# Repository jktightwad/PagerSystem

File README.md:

# Pool table pager

Queue pager system for the office pool table, similar to restaurant pagers.
ESP32 pagers talk to a touchscreen base over ESP-NOW (no Wi-Fi network needed),
charge on a stackable pogo-pin dock, and alert with light, buzzer and vibration.

**All sketches are written but not yet compiled or tested on hardware.**
Arduino-ESP32 core 3.x is required.

## Building with PlatformIO
Each test folder is its own PlatformIO project (`platformio.ini` inside it),
using the pioarduino platform for Arduino-ESP32 core 3.x. Open the folder in
VS Code / PlatformIO and pick the environment for your board:
- `lolin32_lite`: WEMOS LOLIN32 Lite (pagers)
- `esp32c3_supermini`: ESP32-C3 SuperMini (temporary base); not available
  for `pager_alert_test`, whose pins only exist on the classic ESP32

From a terminal: `pio run -e esp32c3_supermini -t upload`, then
`pio device monitor`. The folders also still open in the Arduino IDE.

| Folder | What it is |
|---|---|
| `docs/design.md` | Decisions, proposals, open questions |
| `docs/test_plan.md` | Test cases for pairing, queue, docking, radio, web, security, OTA, power |
| `docs/pager_wiring.md` | Pager pin map, power and driver wiring; PN5180 wiring |
| `range_test/` | ESP-NOW range test (base + walker) |
| `pager_firmware/` | Pager firmware (POC): Wi-Fi setup hotspot, per-pager web page (status, tests, demo mode, admin), OTA |
| `pager_alert_test/` | WS2812 ring, beeper, vibration, button, dock/battery readings |
| `pn5180_csn_test/` | Read the HID iCLASS CSN with a PN5180 (no keys) |
| `base_firmware/` | Base firmware (POC): Wi-Fi from `secrets.h`, status page; queue/badge/radio next |
| `enclosure/` | 3D-printed parts (OpenSCAD): pager shell, LED ring test rig, connector fit tester |
| `ota_test/` | Over-the-air update proof of concept (base AP + pager) |

## Libraries
- Adafruit NeoPixel (1.12+) for `pager_alert_test`
- PN5180 by playfultechnology (GPL-3.0) for `pn5180_csn_test`.
  Don't install ATrappmann's PN5180 library at the same time (same header name).

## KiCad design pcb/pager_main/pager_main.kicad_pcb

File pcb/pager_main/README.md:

# Combined pager board (16 LEDs + ESP32-S3 SuperMini) — draft

**Status: placed, routed, GND stitched; DRC has no clearance or unconnected errors
(remaining: silkscreen overlaps/clipping and 1 single-spoke thermal). Not ordered, not tested.**

| Top | Bottom (seen from below) |
|---|---|
|  |  |

54 x 48 mm, 2 layers, M2 holes in all 4 corners (layout D from `layout_study.py`).

- **Top:** 16 × TUOZHAN TZ-5050S2RGB-5V-I4-H1 (LCSC C26167850, allowed in JLC Economic PCBA; the XINGLIGHT part was Standard-only), evenly spaced (22.5°) on a 20.5 mm radius,
  ring turned 19.75° so every LED keeps its own 100 nF cap beside it, clear of the cut-out.
  Passive SMD buzzer Huaneng MLT-8530 (C94599, 8.5 x 8.5 x 3.0 mm, 16 Ω, 2.7 kHz, PWM tone on GP12;
  four pads, + and − on the right, the two left pads are mechanical dummies) and
  the small parts inside the ring; all JLC-assembled.
- **Under:** SuperMini flat on castellated pads, antenna end at the right edge (no copper
  there); B+/B− soldered from the top through 1.1 × 1.6 mm plated oval holes; an
  L-shaped cut-out only where the module's underside parts are (measured: 3.0–11.2 mm
  from the USB end, incl. 0.5 mm clearance). GND pour (no tracks) allowed under the module. Touch (XH-3) and dock
  (XH-2) right-angle connectors, plugs in from the left edge. SS12F44 switch (slider
  down; end-leg spacing 11.2 mm is an ESTIMATE, slotted). Battery and motor wire pads.
- **Spare pins** on an arc outside the LED ring: top-left TX RX 3 6 7 3V3 GND,
  bottom-left 11 10 9 8 VBAT 3V3 GND (labels on both sides where they fit).
- Connectors: pin 1 = GND (square), power last.

Pins: dock GP1, battery GP2, touch GP4, LEDs GP5 (via 330 Ω), buzzer GP12, motor GP13.

## Rebuild
```
python3 build_main.py
ROUTE_OPTIONAL=GND ROUTE_FIRST=U1 ROUTE_MARGIN=0.08 \
  ROUTE_WIDTHS='{"VBAT": 0.3, "BAT+": 0.4, "POGO5V": 0.3, "MOT_-": 0.3, "GND": 0.25}' \
  python3 ../carrier_s3/route_pcb.py pager_main.kicad_pcb
python3 ../carrier_s3/stitch_gnd.py pager_main.kicad_pcb 2.0
python3 ../carrier_s3/join_gnd.py pager_main.kicad_pcb
python3 ../carrier_s3/remove_dangling.py pager_main.kicad_pcb
python3 fix_anchors.py pager_main.kicad_pcb && python3 check_netlist.py
python3 easyeda_prep.py pager_main.kicad_pcb     # before importing into EasyEDA (and after any refill)
sh export_fab.sh && sh render.sh pcb_top.png pcb_bottom.png
```
Routing takes a while (randomised retries; `ROUTE_SEED` picks the sequence). GND gets tracks
where they fit (routed last, best effort), plus pours on both layers, ~200 stitching vias and
`join_gnd.py` for any piece left over; `remove_dangling.py` drops stitch vias left in pour
islands. The current board is seed 3 with the transistor / divider block ripped up and
re-routed (`../carrier_s3/reroute_area.py`, box 14,19-30,31, GND fan-out vias for R2, R7, Q2,
C1), because those four GND pads were walled in by tracks.

## Assembly
Single-sided JLC Economic PCBA (top side): LEDs, caps, resistors, MOSFETs, diode, buzzer. Hand-soldered:
SuperMini, switch and the two through-hole JST-XH connectors (under the board).
A two-sided variant with SMD connectors (DEALON XH-3PWB / XH-2PWB) can still be built with
`PAGER_SMD_CONN=1 python3 build_main.py` and exported with `sh export_fab.sh smdconn` (Standard PCBA);
its files were removed to avoid uploading the wrong set.

## Current board (v4)
Placement from `build_main.py` (VBAT ring + U2 links pre-drawn). Routed in EasyEDA Pro (autorouter, GND
ignored) and imported with `../carrier_s3/import_dsn_wiring.py`; then: 3V3 link and a 0.4 mm module-B+ feed
(`add_links.py`), GND stubs + vias for boxed-in pads (`pad_vias.py`, local re-route of the nets around R4 / Q1),
ground pours + stitching (`stitch_gnd.py`, `join_gnd.py`, `remove_dangling.py`). Unrouted versions for an
external router are in `for_autorouter/`.

## Panel (3 x 2), not used
`panelize.py` can copy the finished board six times with tabs (`sh export_fab.sh panel` for its JLC
files). Not used: it saved about 4 % on the quote, so the panel files were removed to avoid
uploading the wrong set.

## Review package
`sh make_review.sh` builds `review/` and `review/pager_main_review.zip` for an independent check:
schematic (from `schematic.py`, drawn from `design_main.py`), net list, parts list, design
description with the specific questions, DRC, renders, KiCad and JLC files.

## JLCPCB
`fab/pager_main_gerbers.zip`, `fab/bom_jlc.csv`, `fab/cpl_jlc.csv` (top-side assembly:
LEDs, caps, resistors, MOSFETs, diode). Hand-soldered: SuperMini, switch, buzzer, XH
connectors. **Check LED orientation in JLC's placement preview** (XINGLIGHT package
drawing is an image only; same 5050 4-pin WS2812B pinout).

## Checking before ordering
- `python3 check_netlist.py` compares every pad's net with `design_main.py` (independent of
  the generator).
- `print/top_1to1.pdf` and `print/bottom_1to1_seen_from_below.pdf`: print at 100 % (no
  "fit to page"), check the board outline measures 54 x 48 mm, then lay the real SuperMini,
  switch and XH connectors on them (pin rows, B+/B- holes, cut-out, switch legs).
- In JLC's placement preview: LED pin 1, buzzer +/-, diode stripes, MOSFETs.

## Still to confirm
1. Switch end-leg spacing (11.2 mm assumed).
2. Antenna length (5 mm kept copper-free).
3. Base/ball redesign to fit this board (holes, slider slot, connector access).

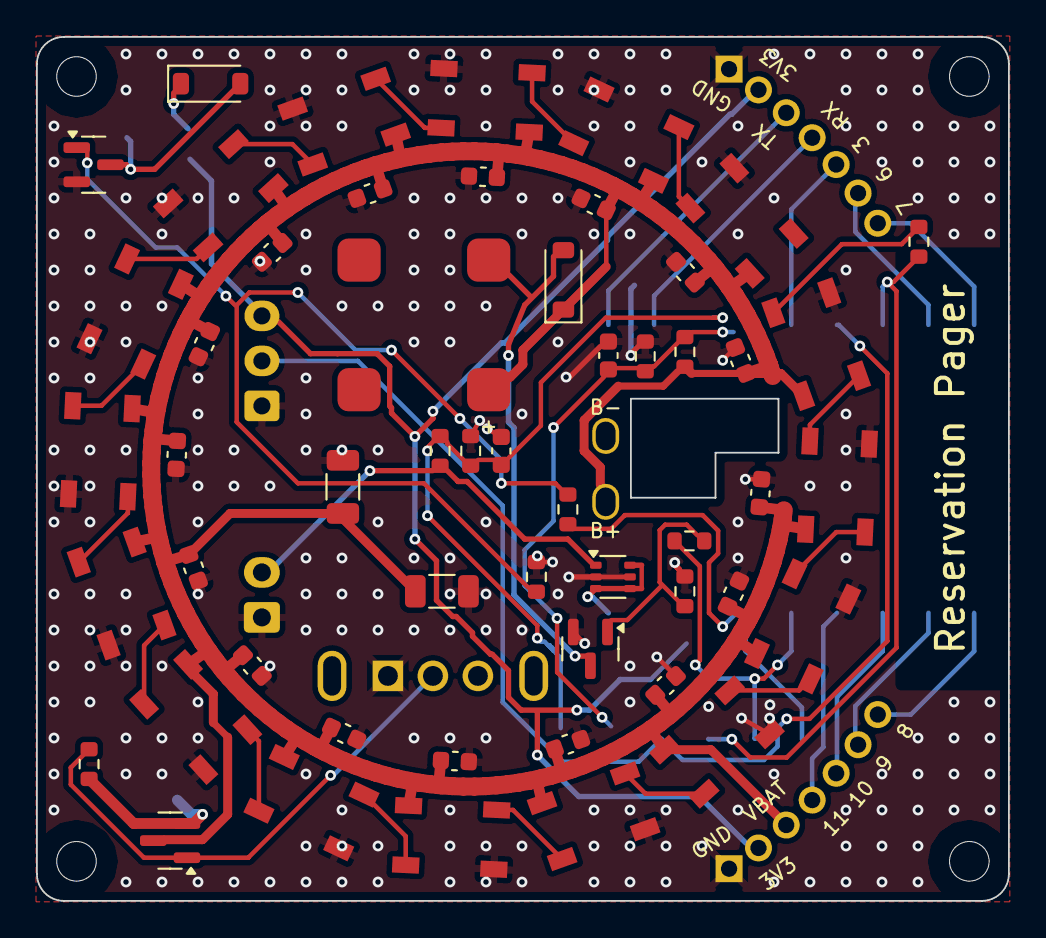
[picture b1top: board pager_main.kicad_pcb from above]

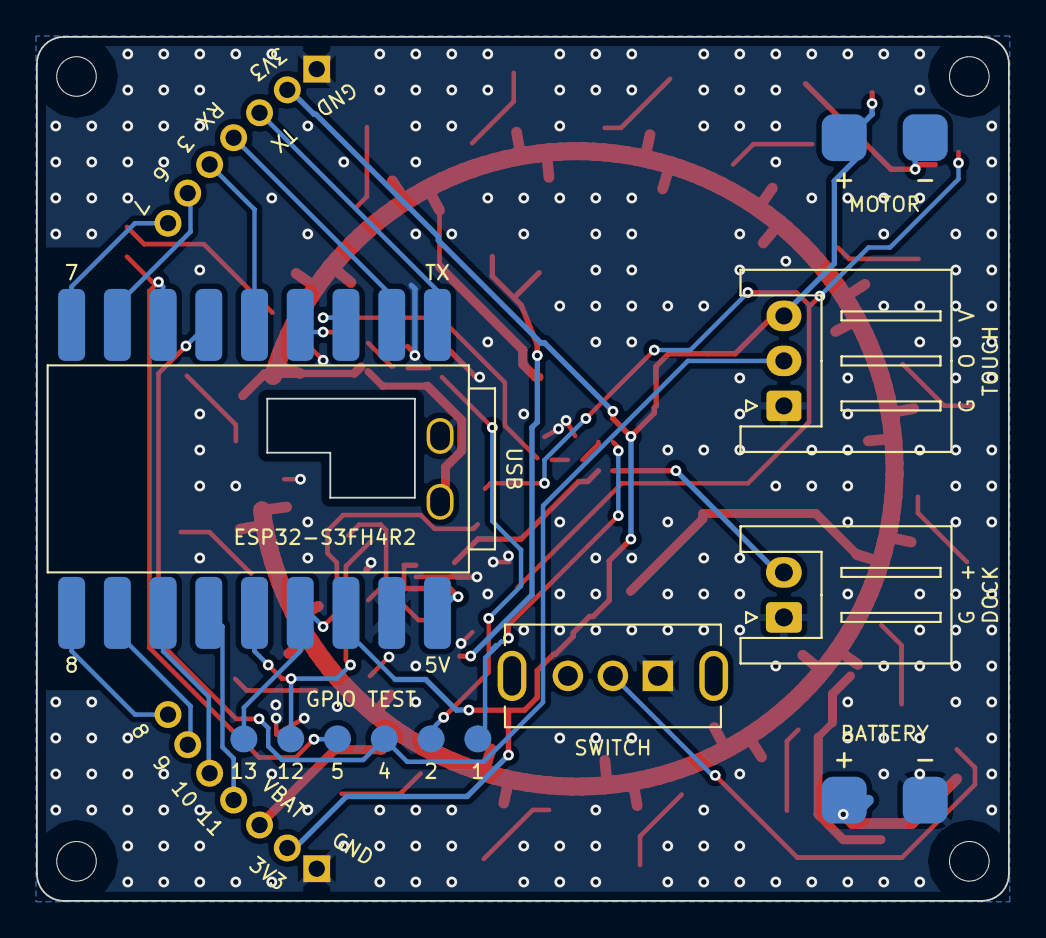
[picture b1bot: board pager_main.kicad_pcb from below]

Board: 2 copper layers, 54.0 x 48.0 mm, 65 parts (2 on the bottom side), 42 nets.

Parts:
BZ1: MLT-8530
C1, C2, C5, C6, C7, C8, C9, C10, C11, C12, C13, C14, C15, C16, C17, C18, C19, C20: 100nF; C_0603_1608Metric
C3, C4: 47uF 10V; C_1206_3216Metric
D1, D3: B5819W; D_SOD-123
J1: Touch; JST_XH_S3B-XH-A_1x03_P2.50mm_Horizontal
J2: Dock (pogo); JST_XH_S2B-XH-A_1x02_P2.50mm_Horizontal
LED1, LED2, LED3, LED4, LED5, LED6, LED7, LED8, LED9, LED10, LED11, LED12, LED13, LED14, LED15, LED16: TZ-5050S2RGB-5V-I4-H1; LED_WS2812B_PLCC4_5.0x5.0mm_P3.2mm
MH1: MH1; MountingHole_2.2mm_M2
MH2: MH2; MountingHole_2.2mm_M2
MH3: MH3; MountingHole_2.2mm_M2
MH4: MH4; MountingHole_2.2mm_M2
P1: Battery pads
P2: Motor pads
P3: spare pins / power
Q1, Q2: AO3400A; SOT-23
Q3: AO3401A; SOT-23
R1, R3, R5: 330Ω; R_0603_1608Metric
R2, R4, R6, R7, R8, R9, R10: 100kΩ; R_0603_1608Metric
SW1: SS12F44-G3 slide switch
TP1: GPIO test points
U1: ESP32-S3 SuperMini
U2: LM66100DCKR; SOT-363_SC-70-6

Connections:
3V3: D1.1, J1.3, P2.2, P3.6, P3.13, U1.3V3
BAT+: P1.2, Q3.2, R10.1
BAT_SENSE: C1.1, R6.2, R7.1, TP1.2, U1.GP2
BUZ_-: BZ1.2, D3.2, Q1.3
BUZ_G: Q1.1, R1.2, R2.1
BUZ_IO: R1.1, TP1.5, U1.GP12
DOCK_SENSE: C2.1, R8.2, R9.1, TP1.1, U1.GP1
GND: C1.2, C2.2, C3.2, C4.2, C5.2, C6.2, C7.2, C8.2, C9.2, C10.2, C11.2, C12.2, C13.2, C14.2, C15.2, C16.2, C17.2, C18.2, C19.2, C20.2, J1.1, J2.1, LED1.3, LED2.3, LED3.3, LED4.3, LED5.3, LED6.3, LED7.3, LED8.3, LED9.3, LED10.3, LED11.3, LED12.3, LED13.3, LED14.3, LED15.3, LED16.3, P1.1, P3.7, P3.14, Q1.2, Q2.2, R2.2, R4.2, R7.2, R9.2, SW1.1, U1.B-, U1.GND, U2.2, U2.5
LED_D1: LED1.2, LED2.4
LED_D2: LED2.2, LED3.4
LED_D3: LED3.2, LED4.4
LED_D4: LED4.2, LED5.4
LED_D5: LED5.2, LED6.4
LED_D6: LED6.2, LED7.4
LED_D7: LED7.2, LED8.4
LED_D8: LED8.2, LED9.4
LED_D9: LED9.2, LED10.4
LED_D10: LED10.2, LED11.4
LED_D11: LED11.2, LED12.4
LED_D12: LED12.2, LED13.4
LED_D13: LED13.2, LED14.4
LED_D14: LED14.2, LED15.4
LED_D15: LED15.2, LED16.4
LED_DIN: LED1.4, R5.2
MOD5V: U1.5V, U2.3, U2.4, U2.6
MOT_-: D1.2, P2.1, Q2.3
MOT_G: Q2.1, R3.2, R4.1
MOT_IO: R3.1, TP1.6, U1.GP13
POGO5V: J2.2, R8.1, U2.1
RING_IO: R5.1, TP1.4, U1.GP5
SPARE_GP3: P3.3, U1.GP3
SPARE_GP6: P3.2, U1.GP6
SPARE_GP7: P3.1, U1.GP7
SPARE_GP8: P3.8, U1.GP8
SPARE_GP9: P3.9, U1.GP9
SPARE_GP10: P3.10, U1.GP10
SPARE_GP11: P3.11, U1.GP11
SPARE_RX: P3.4, U1.RX
SPARE_TX: P3.5, U1.TX
SW_G: Q3.1, R10.2, SW1.2
TOUCH: J1.2, TP1.3, U1.GP4
VBAT: BZ1.1, C3.1, C4.1, C5.1, C6.1, C7.1, C8.1, C9.1, C10.1, C11.1, C12.1, C13.1, C14.1, C15.1, C16.1, C17.1, C18.1, C19.1, C20.1, D3.1, LED1.1, LED2.1, LED3.1, LED4.1, LED5.1, LED6.1, LED7.1, LED8.1, LED9.1, LED10.1, LED11.1, LED12.1, LED13.1, LED14.1, LED15.1, LED16.1, P3.12, Q3.3, R6.1, U1.B+

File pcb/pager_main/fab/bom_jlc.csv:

Comment,Designator,Footprint,LCSC Part #
100kΩ,"R2,R4,R6,R7,R8,R9,R10",0603,C25803
100nF,"C1,C2,C5,C6,C7,C8,C9,C10,C11,C12,C13,C14,C15,C16,C17,C18,C19,C20",0603,C14663
330Ω,"R1,R3,R5",0603,C23138
47uF 10V,"C3,C4",1206,C96123
AO3400A,"Q1,Q2",SOT-23,C20917
AO3401A,Q3,SOT-23,C15127
B5819W,"D1,D3",SOD-123,C8598
LM66100DCKR,U2,SC-70-6,C2869734
MLT-8530,BZ1,SMD 8.5x8.5,C94599
TZ-5050S2RGB-5V-I4-H1,"LED1,LED2,LED3,LED4,LED5,LED6,LED7,LED8,LED9,LED10,LED11,LED12,LED13,LED14,LED15,LED16",5050,C26167850

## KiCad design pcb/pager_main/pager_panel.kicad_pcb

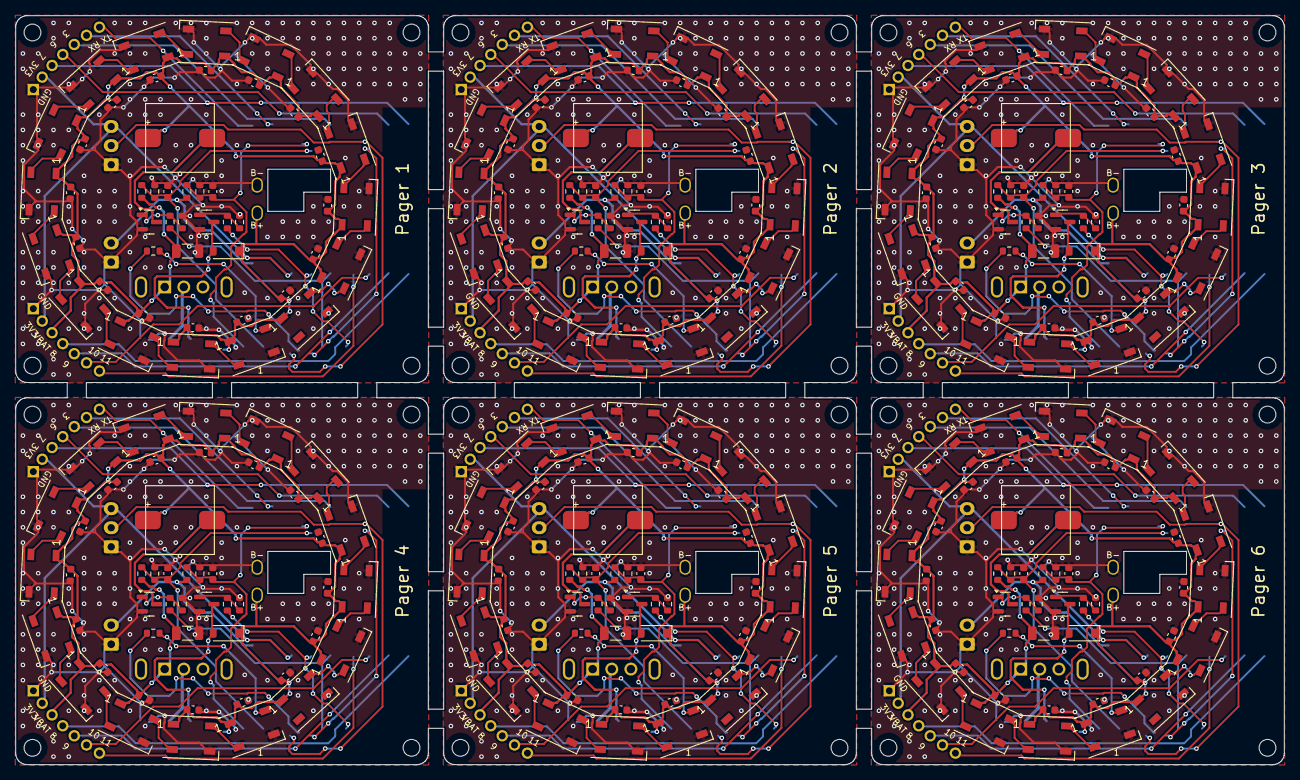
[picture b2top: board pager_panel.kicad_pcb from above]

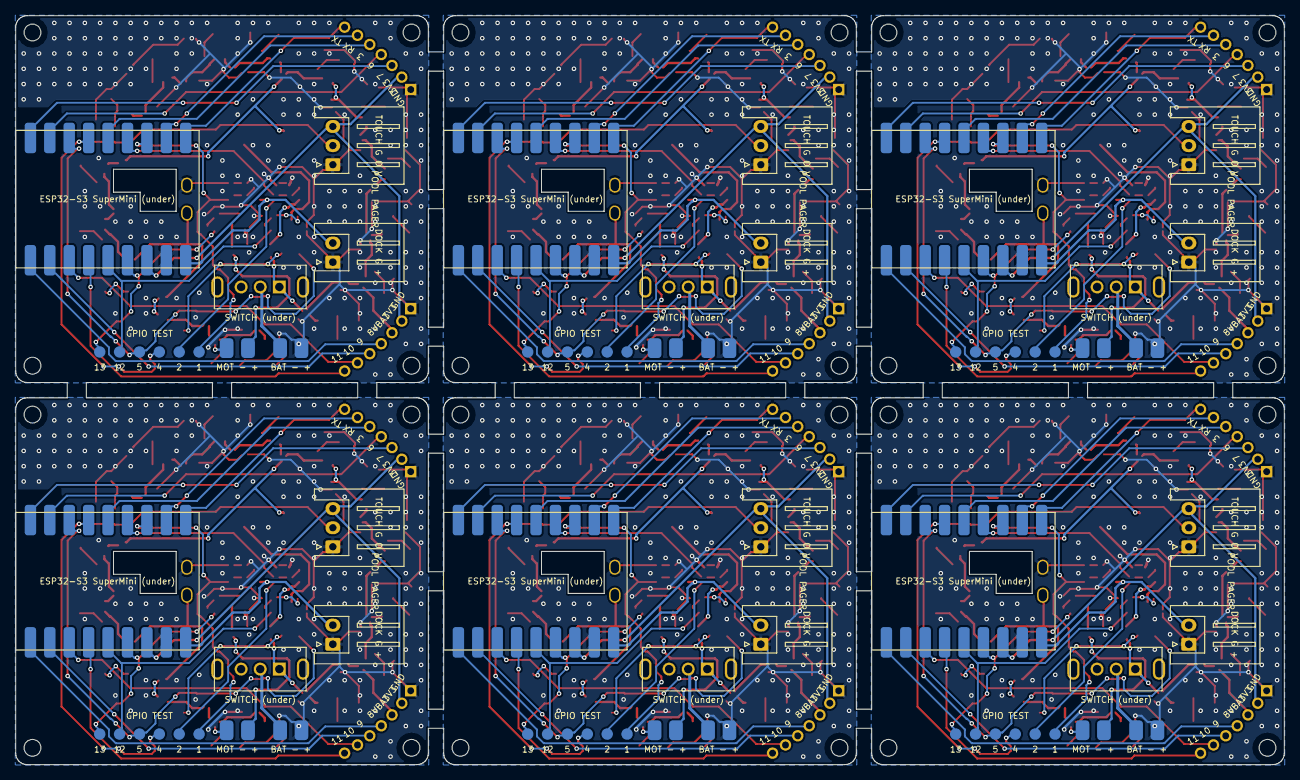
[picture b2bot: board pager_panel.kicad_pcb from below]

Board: 2 copper layers, 166.0 x 98.0 mm, 360 parts (12 on the bottom side), 240 nets.

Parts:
BZ1_1, BZ1_2, BZ1_3, BZ1_4, BZ1_5, BZ1_6: SMD-0955-05-27
C1_1, C1_2, C1_3, C1_4, C1_5, C1_6, C2_1, C2_2, C2_3, C2_4, C2_5, C2_6: 100nF; C_0603_1608Metric
C3_1, C3_2, C3_3, C3_4, C3_5, C3_6: 47uF 10V; C_1206_3216Metric
CL1_1, CL1_2, CL1_3, CL1_4, CL1_5, CL1_6, CL2_1, CL2_2, CL2_3, CL2_4, CL2_5, CL2_6, CL3_1, CL3_2, CL3_3, CL3_4, CL3_5, CL3_6, CL4_1, CL4_2, CL4_3, CL4_4, CL4_5, CL4_6, CL5_1, CL5_2, CL5_3, CL5_4, CL5_5, CL5_6, CL6_1, CL6_2, CL6_3, CL6_4, CL6_5, CL6_6, CL7_1, CL7_2, CL7_3, CL7_4, CL7_5, CL7_6, CL8_1, CL8_2, CL8_3, CL8_4, CL8_5, CL8_6, CL9_1, CL9_2, CL9_3, CL9_4, CL9_5, CL9_6, CL10_1, CL10_2, CL10_3, CL10_4, CL10_5, CL10_6, CL11_1, CL11_2, CL11_3, CL11_4, CL11_5, CL11_6, CL12_1, CL12_2, CL12_3, CL12_4, CL12_5, CL12_6, CL13_1, CL13_2, CL13_3, CL13_4, CL13_5, CL13_6, CL14_1, CL14_2, CL14_3, CL14_4, CL14_5, CL14_6, CL15_1, CL15_2, CL15_3, CL15_4, CL15_5, CL15_6, CL16_1, CL16_2, CL16_3, CL16_4, CL16_5, CL16_6: 100nF; C_0603_1608Metric
D1_1, D1_2, D1_3, D1_4, D1_5, D1_6: B5819W; D_SOD-123
J1_1, J1_2, J1_3, J1_4, J1_5, J1_6: Touch; JST_XH_S3B-XH-A_1x03_P2.50mm_Horizontal
J2_1, J2_2, J2_3, J2_4, J2_5, J2_6: Dock (pogo); JST_XH_S2B-XH-A_1x02_P2.50mm_Horizontal
LED1_1, LED1_2, LED1_3, LED1_4, LED1_5, LED1_6, LED2_1, LED2_2, LED2_3, LED2_4, LED2_5, LED2_6, LED3_1, LED3_2, LED3_3, LED3_4, LED3_5, LED3_6, LED4_1, LED4_2, LED4_3, LED4_4, LED4_5, LED4_6, LED5_1, LED5_2, LED5_3, LED5_4, LED5_5, LED5_6, LED6_1, LED6_2, LED6_3, LED6_4, LED6_5, LED6_6, LED7_1, LED7_2, LED7_3, LED7_4, LED7_5, LED7_6, LED8_1, LED8_2, LED8_3, LED8_4, LED8_5, LED8_6, LED9_1, LED9_2, LED9_3, LED9_4, LED9_5, LED9_6, LED10_1, LED10_2, LED10_3, LED10_4, LED10_5, LED10_6, LED11_1, LED11_2, LED11_3, LED11_4, LED11_5, LED11_6, LED12_1, LED12_2, LED12_3, LED12_4, LED12_5, LED12_6, LED13_1, LED13_2, LED13_3, LED13_4, LED13_5, LED13_6, LED14_1, LED14_2, LED14_3, LED14_4, LED14_5, LED14_6, LED15_1, LED15_2, LED15_3, LED15_4, LED15_5, LED15_6, LED16_1, LED16_2, LED16_3, LED16_4, LED16_5, LED16_6: TZ-5050S2RGB-5V-I4-H1; LED_WS2812B_PLCC4_5.0x5.0mm_P3.2mm
MH1_1, MH1_2, MH1_3, MH1_4, MH1_5, MH1_6: MH1; MountingHole_2.2mm_M2
MH2_1, MH2_2, MH2_3, MH2_4, MH2_5, MH2_6: MH2; MountingHole_2.2mm_M2
MH3_1, MH3_2, MH3_3, MH3_4, MH3_5, MH3_6: MH3; MountingHole_2.2mm_M2
MH4_1, MH4_2, MH4_3, MH4_4, MH4_5, MH4_6: MH4; MountingHole_2.2mm_M2
P1_1, P1_2, P1_3, P1_4, P1_5, P1_6: Battery pads
P2_1, P2_2, P2_3, P2_4, P2_5, P2_6: Motor pads
P3_1, P3_2, P3_3, P3_4, P3_5, P3_6: spare pins / power
Q1_1, Q1_2, Q1_3, Q1_4, Q1_5, Q1_6, Q2_1, Q2_2, Q2_3, Q2_4, Q2_5, Q2_6: AO3400A; SOT-23
R1_1, R1_2, R1_3, R1_4, R1_5, R1_6, R3_1, R3_2, R3_3, R3_4, R3_5, R3_6, R5_1, R5_2, R5_3, R5_4, R5_5, R5_6: 330R; R_0603_1608Metric
R2_1, R2_2, R2_3, R2_4, R2_5, R2_6, R4_1, R4_2, R4_3, R4_4, R4_5, R4_6, R6_1, R6_2, R6_3, R6_4, R6_5, R6_6, R7_1, R7_2, R7_3, R7_4, R7_5, R7_6, R8_1, R8_2, R8_3, R8_4, R8_5, R8_6, R9_1, R9_2, R9_3, R9_4, R9_5, R9_6: 100k; R_0603_1608Metric
SW1_1, SW1_2, SW1_3, SW1_4, SW1_5, SW1_6: SS12F44-G3 slide switch
TP1_1, TP1_2, TP1_3, TP1_4, TP1_5, TP1_6: GPIO test points
U1_1, U1_2, U1_3, U1_4, U1_5, U1_6: ESP32-S3 SuperMini

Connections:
P1/3V3: J1_1.3, P3_1.6, P3_1.13, U1_1.3V3
P1/BAT+: P1_1.2, SW1_1.2
P1/BAT_SENSE: C1_1.1, R6_1.2, R7_1.1, TP1_1.2, U1_1.GP2
P1/BUZ_-: BZ1_1.2, Q1_1.3
P1/BUZ_G: Q1_1.1, R1_1.2, R2_1.1
P1/BUZ_IO: R1_1.1, TP1_1.5, U1_1.GP12
P1/DOCK_SENSE: C2_1.1, R8_1.2, R9_1.1, TP1_1.1, U1_1.GP1
P1/GND: C1_1.2, C2_1.2, C3_1.2, CL1_1.2, CL2_1.2, CL3_1.2, CL4_1.2, CL5_1.2, CL6_1.2, CL7_1.2, CL8_1.2, CL9_1.2, CL10_1.2, CL11_1.2, CL12_1.2, CL13_1.2, CL14_1.2, CL15_1.2, CL16_1.2, J1_1.1, J2_1.1, LED1_1.3, LED2_1.3, LED3_1.3, LED4_1.3, LED5_1.3, LED6_1.3, LED7_1.3, LED8_1.3, LED9_1.3, LED10_1.3, LED11_1.3, LED12_1.3, LED13_1.3, LED14_1.3, LED15_1.3, LED16_1.3, P1_1.1, P3_1.7, P3_1.14, Q1_1.2, Q2_1.2, R2_1.2, R4_1.2, R7_1.2, R9_1.2, U1_1.B-, U1_1.GND
P1/LED_D1: LED1_1.2, LED2_1.4
P1/LED_D2: LED2_1.2, LED3_1.4
P1/LED_D3: LED3_1.2, LED4_1.4
P1/LED_D4: LED4_1.2, LED5_1.4
P1/LED_D5: LED5_1.2, LED6_1.4
P1/LED_D6: LED6_1.2, LED7_1.4
P1/LED_D7: LED7_1.2, LED8_1.4
P1/LED_D8: LED8_1.2, LED9_1.4
P1/LED_D9: LED9_1.2, LED10_1.4
P1/LED_D10: LED10_1.2, LED11_1.4
P1/LED_D11: LED11_1.2, LED12_1.4
P1/LED_D12: LED12_1.2, LED13_1.4
P1/LED_D13: LED13_1.2, LED14_1.4
P1/LED_D14: LED14_1.2, LED15_1.4
P1/LED_D15: LED15_1.2, LED16_1.4
P1/LED_DIN: LED1_1.4, R5_1.2
P1/MOT_-: D1_1.2, P2_1.1, Q2_1.3
P1/MOT_G: Q2_1.1, R3_1.2, R4_1.1
P1/MOT_IO: R3_1.1, TP1_1.6, U1_1.GP13
P1/POGO5V: J2_1.2, R8_1.1, U1_1.5V
P1/RING_IO: R5_1.1, TP1_1.4, U1_1.GP5
P1/SPARE_GP3: P3_1.3, U1_1.GP3
P1/SPARE_GP6: P3_1.4, U1_1.GP6
P1/SPARE_GP7: P3_1.5, U1_1.GP7
P1/SPARE_GP8: P3_1.11, U1_1.GP8
P1/SPARE_GP9: P3_1.10, U1_1.GP9
P1/SPARE_GP10: P3_1.9, U1_1.GP10
P1/SPARE_GP11: P3_1.8, U1_1.GP11
P1/SPARE_RX: P3_1.2, U1_1.RX
P1/SPARE_TX: P3_1.1, U1_1.TX
P1/TOUCH: J1_1.2, TP1_1.3, U1_1.GP4
P1/VBAT: BZ1_1.1, C3_1.1, CL1_1.1, CL2_1.1, CL3_1.1, CL4_1.1, CL5_1.1, CL6_1.1, CL7_1.1, CL8_1.1, CL9_1.1, CL10_1.1, CL11_1.1, CL12_1.1, CL13_1.1, CL14_1.1, CL15_1.1, CL16_1.1, D1_1.1, LED1_1.1, LED2_1.1, LED3_1.1, LED4_1.1, LED5_1.1, LED6_1.1, LED7_1.1, LED8_1.1, LED9_1.1, LED10_1.1, LED11_1.1, LED12_1.1, LED13_1.1, LED14_1.1, LED15_1.1, LED16_1.1, P2_1.2, P3_1.12, R6_1.1, SW1_1.1, U1_1.B+
P2/3V3: J1_2.3, P3_2.6, P3_2.13, U1_2.3V3
P2/BAT+: P1_2.2, SW1_2.2
P2/BAT_SENSE: C1_2.1, R6_2.2, R7_2.1, TP1_2.2, U1_2.GP2
P2/BUZ_-: BZ1_2.2, Q1_2.3
P2/BUZ_G: Q1_2.1, R1_2.2, R2_2.1
P2/BUZ_IO: R1_2.1, TP1_2.5, U1_2.GP12
P2/DOCK_SENSE: C2_2.1, R8_2.2, R9_2.1, TP1_2.1, U1_2.GP1
P2/GND: C1_2.2, C2_2.2, C3_2.2, CL1_2.2, CL2_2.2, CL3_2.2, CL4_2.2, CL5_2.2, CL6_2.2, CL7_2.2, CL8_2.2, CL9_2.2, CL10_2.2, CL11_2.2, CL12_2.2, CL13_2.2, CL14_2.2, CL15_2.2, CL16_2.2, J1_2.1, J2_2.1, LED1_2.3, LED2_2.3, LED3_2.3, LED4_2.3, LED5_2.3, LED6_2.3, LED7_2.3, LED8_2.3, LED9_2.3, LED10_2.3, LED11_2.3, LED12_2.3, LED13_2.3, LED14_2.3, LED15_2.3, LED16_2.3, P1_2.1, P3_2.7, P3_2.14, Q1_2.2, Q2_2.2, R2_2.2, R4_2.2, R7_2.2, R9_2.2, U1_2.B-, U1_2.GND
P2/LED_D1: LED1_2.2, LED2_2.4
P2/LED_D2: LED2_2.2, LED3_2.4
P2/LED_D3: LED3_2.2, LED4_2.4
P2/LED_D4: LED4_2.2, LED5_2.4
P2/LED_D5: LED5_2.2, LED6_2.4
P2/LED_D6: LED6_2.2, LED7_2.4
P2/LED_D7: LED7_2.2, LED8_2.4
P2/LED_D8: LED8_2.2, LED9_2.4
P2/LED_D9: LED9_2.2, LED10_2.4
P2/LED_D10: LED10_2.2, LED11_2.4
P2/LED_D11: LED11_2.2, LED12_2.4
P2/LED_D12: LED12_2.2, LED13_2.4
P2/LED_D13: LED13_2.2, LED14_2.4
P2/LED_D14: LED14_2.2, LED15_2.4
P2/LED_D15: LED15_2.2, LED16_2.4
P2/LED_DIN: LED1_2.4, R5_2.2
P2/MOT_-: D1_2.2, P2_2.1, Q2_2.3
P2/MOT_G: Q2_2.1, R3_2.2, R4_2.1
P2/MOT_IO: R3_2.1, TP1_2.6, U1_2.GP13
P2/POGO5V: J2_2.2, R8_2.1, U1_2.5V
P2/RING_IO: R5_2.1, TP1_2.4, U1_2.GP5
P2/SPARE_GP3: P3_2.3, U1_2.GP3
P2/SPARE_GP6: P3_2.4, U1_2.GP6
P2/SPARE_GP7: P3_2.5, U1_2.GP7
P2/SPARE_GP8: P3_2.11, U1_2.GP8
P2/SPARE_GP9: P3_2.10, U1_2.GP9
P2/SPARE_GP10: P3_2.9, U1_2.GP10
P2/SPARE_GP11: P3_2.8, U1_2.GP11
P2/SPARE_RX: P3_2.2, U1_2.RX
P2/SPARE_TX: P3_2.1, U1_2.TX
P2/TOUCH: J1_2.2, TP1_2.3, U1_2.GP4
P2/VBAT: BZ1_2.1, C3_2.1, CL1_2.1, CL2_2.1, CL3_2.1, CL4_2.1, CL5_2.1, CL6_2.1, CL7_2.1, CL8_2.1, CL9_2.1, CL10_2.1, CL11_2.1, CL12_2.1, CL13_2.1, CL14_2.1, CL15_2.1, CL16_2.1, D1_2.1, LED1_2.1, LED2_2.1, LED3_2.1, LED4_2.1, LED5_2.1, LED6_2.1, LED7_2.1, LED8_2.1, LED9_2.1, LED10_2.1, LED11_2.1, LED12_2.1, LED13_2.1, LED14_2.1, LED15_2.1, LED16_2.1, P2_2.2, P3_2.12, R6_2.1, SW1_2.1, U1_2.B+
P3/3V3: J1_3.3, P3_3.6, P3_3.13, U1_3.3V3
P3/BAT+: P1_3.2, SW1_3.2
P3/BAT_SENSE: C1_3.1, R6_3.2, R7_3.1, TP1_3.2, U1_3.GP2
P3/BUZ_-: BZ1_3.2, Q1_3.3
P3/BUZ_G: Q1_3.1, R1_3.2, R2_3.1
P3/BUZ_IO: R1_3.1, TP1_3.5, U1_3.GP12
P3/DOCK_SENSE: C2_3.1, R8_3.2, R9_3.1, TP1_3.1, U1_3.GP1
P3/GND: C1_3.2, C2_3.2, C3_3.2, CL1_3.2, CL2_3.2, CL3_3.2, CL4_3.2, CL5_3.2, CL6_3.2, CL7_3.2, CL8_3.2, CL9_3.2, CL10_3.2, CL11_3.2, CL12_3.2, CL13_3.2, CL14_3.2, CL15_3.2, CL16_3.2, J1_3.1, J2_3.1, LED1_3.3, LED2_3.3, LED3_3.3, LED4_3.3, LED5_3.3, LED6_3.3, LED7_3.3, LED8_3.3, LED9_3.3, LED10_3.3, LED11_3.3, LED12_3.3, LED13_3.3, LED14_3.3, LED15_3.3, LED16_3.3, P1_3.1, P3_3.7, P3_3.14, Q1_3.2, Q2_3.2, R2_3.2, R4_3.2, R7_3.2, R9_3.2, U1_3.B-, U1_3.GND
P3/LED_D1: LED1_3.2, LED2_3.4
P3/LED_D2: LED2_3.2, LED3_3.4
P3/LED_D3: LED3_3.2, LED4_3.4
P3/LED_D4: LED4_3.2, LED5_3.4
P3/LED_D5: LED5_3.2, LED6_3.4
P3/LED_D6: LED6_3.2, LED7_3.4
P3/LED_D7: LED7_3.2, LED8_3.4
P3/LED_D8: LED8_3.2, LED9_3.4
P3/LED_D9: LED9_3.2, LED10_3.4
P3/LED_D10: LED10_3.2, LED11_3.4
P3/LED_D11: LED11_3.2, LED12_3.4
P3/LED_D12: LED12_3.2, LED13_3.4
P3/LED_D13: LED13_3.2, LED14_3.4
P3/LED_D14: LED14_3.2, LED15_3.4
P3/LED_D15: LED15_3.2, LED16_3.4
P3/LED_DIN: LED1_3.4, R5_3.2
P3/MOT_-: D1_3.2, P2_3.1, Q2_3.3
P3/MOT_G: Q2_3.1, R3_3.2, R4_3.1
P3/MOT_IO: R3_3.1, TP1_3.6, U1_3.GP13
P3/POGO5V: J2_3.2, R8_3.1, U1_3.5V
P3/RING_IO: R5_3.1, TP1_3.4, U1_3.GP5
P3/SPARE_GP3: P3_3.3, U1_3.GP3
P3/SPARE_GP6: P3_3.4, U1_3.GP6
P3/SPARE_GP7: P3_3.5, U1_3.GP7
P3/SPARE_GP8: P3_3.11, U1_3.GP8
P3/SPARE_GP9: P3_3.10, U1_3.GP9
P3/SPARE_GP10: P3_3.9, U1_3.GP10
P3/SPARE_GP11: P3_3.8, U1_3.GP11
P3/SPARE_RX: P3_3.2, U1_3.RX
P3/SPARE_TX: P3_3.1, U1_3.TX
P3/TOUCH: J1_3.2, TP1_3.3, U1_3.GP4
P3/VBAT: BZ1_3.1, C3_3.1, CL1_3.1, CL2_3.1, CL3_3.1, CL4_3.1, CL5_3.1, CL6_3.1, CL7_3.1, CL8_3.1, CL9_3.1, CL10_3.1, CL11_3.1, CL12_3.1, CL13_3.1, CL14_3.1, CL15_3.1, CL16_3.1, D1_3.1, LED1_3.1, LED2_3.1, LED3_3.1, LED4_3.1, LED5_3.1, LED6_3.1, LED7_3.1, LED8_3.1, LED9_3.1, LED10_3.1, LED11_3.1, LED12_3.1, LED13_3.1, LED14_3.1, LED15_3.1, LED16_3.1, P2_3.2, P3_3.12, R6_3.1, SW1_3.1, U1_3.B+
P4/3V3: J1_4.3, P3_4.6, P3_4.13, U1_4.3V3
P4/BAT+: P1_4.2, SW1_4.2
P4/BAT_SENSE: C1_4.1, R6_4.2, R7_4.1, TP1_4.2, U1_4.GP2
P4/BUZ_-: BZ1_4.2, Q1_4.3
P4/BUZ_G: Q1_4.1, R1_4.2, R2_4.1
P4/BUZ_IO: R1_4.1, TP1_4.5, U1_4.GP12
P4/DOCK_SENSE: C2_4.1, R8_4.2, R9_4.1, TP1_4.1, U1_4.GP1
P4/GND: C1_4.2, C2_4.2, C3_4.2, CL1_4.2, CL2_4.2, CL3_4.2, CL4_4.2, CL5_4.2, CL6_4.2, CL7_4.2, CL8_4.2, CL9_4.2, CL10_4.2, CL11_4.2, CL12_4.2, CL13_4.2, CL14_4.2, CL15_4.2, CL16_4.2, J1_4.1, J2_4.1, LED1_4.3, LED2_4.3, LED3_4.3, LED4_4.3, LED5_4.3, LED6_4.3, LED7_4.3, LED8_4.3, LED9_4.3, LED10_4.3, LED11_4.3, LED12_4.3, LED13_4.3, LED14_4.3, LED15_4.3, LED16_4.3, P1_4.1, P3_4.7, P3_4.14, Q1_4.2, Q2_4.2, R2_4.2, R4_4.2, R7_4.2, R9_4.2, U1_4.B-, U1_4.GND
P4/LED_D1: LED1_4.2, LED2_4.4
P4/LED_D2: LED2_4.2, LED3_4.4
P4/LED_D3: LED3_4.2, LED4_4.4
P4/LED_D4: LED4_4.2, LED5_4.4
P4/LED_D5: LED5_4.2, LED6_4.4
P4/LED_D6: LED6_4.2, LED7_4.4
P4/LED_D7: LED7_4.2, LED8_4.4
P4/LED_D8: LED8_4.2, LED9_4.4
P4/LED_D9: LED9_4.2, LED10_4.4
P4/LED_D10: LED10_4.2, LED11_4.4
P4/LED_D11: LED11_4.2, LED12_4.4
P4/LED_D12: LED12_4.2, LED13_4.4
P4/LED_D13: LED13_4.2, LED14_4.4
P4/LED_D14: LED14_4.2, LED15_4.4
P4/LED_D15: LED15_4.2, LED16_4.4
P4/LED_DIN: LED1_4.4, R5_4.2
P4/MOT_-: D1_4.2, P2_4.1, Q2_4.3
P4/MOT_G: Q2_4.1, R3_4.2, R4_4.1
P4/MOT_IO: R3_4.1, TP1_4.6, U1_4.GP13
P4/POGO5V: J2_4.2, R8_4.1, U1_4.5V
P4/RING_IO: R5_4.1, TP1_4.4, U1_4.GP5
P4/SPARE_GP3: P3_4.3, U1_4.GP3
P4/SPARE_GP6: P3_4.4, U1_4.GP6
P4/SPARE_GP7: P3_4.5, U1_4.GP7
P4/SPARE_GP8: P3_4.11, U1_4.GP8
P4/SPARE_GP9: P3_4.10, U1_4.GP9
P4/SPARE_GP10: P3_4.9, U1_4.GP10
P4/SPARE_GP11: P3_4.8, U1_4.GP11
P4/SPARE_RX: P3_4.2, U1_4.RX
P4/SPARE_TX: P3_4.1, U1_4.TX
P4/TOUCH: J1_4.2, TP1_4.3, U1_4.GP4
P4/VBAT: BZ1_4.1, C3_4.1, CL1_4.1, CL2_4.1, CL3_4.1, CL4_4.1, CL5_4.1, CL6_4.1, CL7_4.1, CL8_4.1, CL9_4.1, CL10_4.1, CL11_4.1, CL12_4.1, CL13_4.1, CL14_4.1, CL15_4.1, CL16_4.1, D1_4.1, LED1_4.1, LED2_4.1, LED3_4.1, LED4_4.1, LED5_4.1, LED6_4.1, LED7_4.1, LED8_4.1, LED9_4.1, LED10_4.1, LED11_4.1, LED12_4.1, LED13_4.1, LED14_4.1, LED15_4.1, LED16_4.1, P2_4.2, P3_4.12, R6_4.1, SW1_4.1, U1_4.B+
P5/3V3: J1_5.3, P3_5.6, P3_5.13, U1_5.3V3
P5/BAT+: P1_5.2, SW1_5.2
P5/BAT_SENSE: C1_5.1, R6_5.2, R7_5.1, TP1_5.2, U1_5.GP2
P5/BUZ_-: BZ1_5.2, Q1_5.3
P5/BUZ_G: Q1_5.1, R1_5.2, R2_5.1
P5/BUZ_IO: R1_5.1, TP1_5.5, U1_5.GP12
P5/DOCK_SENSE: C2_5.1, R8_5.2, R9_5.1, TP1_5.1, U1_5.GP1
P5/GND: C1_5.2, C2_5.2, C3_5.2, CL1_5.2, CL2_5.2, CL3_5.2, CL4_5.2, CL5_5.2, CL6_5.2, CL7_5.2, CL8_5.2, CL9_5.2, CL10_5.2, CL11_5.2, CL12_5.2, CL13_5.2, CL14_5.2, CL15_5.2, CL16_5.2, J1_5.1, J2_5.1, LED1_5.3, LED2_5.3, LED3_5.3, LED4_5.3, LED5_5.3, LED6_5.3, LED7_5.3, LED8_5.3, LED9_5.3, LED10_5.3, LED11_5.3, LED12_5.3, LED13_5.3, LED14_5.3, LED15_5.3, LED16_5.3, P1_5.1, P3_5.7, P3_5.14, Q1_5.2, Q2_5.2, R2_5.2, R4_5.2, R7_5.2, R9_5.2, U1_5.B-, U1_5.GND
P5/LED_D1: LED1_5.2, LED2_5.4
P5/LED_D2: LED2_5.2, LED3_5.4
P5/LED_D3: LED3_5.2, LED4_5.4
P5/LED_D4: LED4_5.2, LED5_5.4
P5/LED_D5: LED5_5.2, LED6_5.4
P5/LED_D6: LED6_5.2, LED7_5.4
P5/LED_D7: LED7_5.2, LED8_5.4
P5/LED_D8: LED8_5.2, LED9_5.4
P5/LED_D9: LED9_5.2, LED10_5.4
P5/LED_D10: LED10_5.2, LED11_5.4
P5/LED_D11: LED11_5.2, LED12_5.4
P5/LED_D12: LED12_5.2, LED13_5.4
P5/LED_D13: LED13_5.2, LED14_5.4
P5/LED_D14: LED14_5.2, LED15_5.4
P5/LED_D15: LED15_5.2, LED16_5.4
P5/LED_DIN: LED1_5.4, R5_5.2
P5/MOT_-: D1_5.2, P2_5.1, Q2_5.3
P5/MOT_G: Q2_5.1, R3_5.2, R4_5.1
P5/MOT_IO: R3_5.1, TP1_5.6, U1_5.GP13
P5/POGO5V: J2_5.2, R8_5.1, U1_5.5V
P5/RING_IO: R5_5.1, TP1_5.4, U1_5.GP5
P5/SPARE_GP3: P3_5.3, U1_5.GP3
P5/SPARE_GP6: P3_5.4, U1_5.GP6
P5/SPARE_GP7: P3_5.5, U1_5.GP7
P5/SPARE_GP8: P3_5.11, U1_5.GP8
P5/SPARE_GP9: P3_5.10, U1_5.GP9
P5/SPARE_GP10: P3_5.9, U1_5.GP10
P5/SPARE_GP11: P3_5.8, U1_5.GP11
P5/SPARE_RX: P3_5.2, U1_5.RX
P5/SPARE_TX: P3_5.1, U1_5.TX
P5/TOUCH: J1_5.2, TP1_5.3, U1_5.GP4
P5/VBAT: BZ1_5.1, C3_5.1, CL1_5.1, CL2_5.1, CL3_5.1, CL4_5.1, CL5_5.1, CL6_5.1, CL7_5.1, CL8_5.1, CL9_5.1, CL10_5.1, CL11_5.1, CL12_5.1, CL13_5.1, CL14_5.1, CL15_5.1, CL16_5.1, D1_5.1, LED1_5.1, LED2_5.1, LED3_5.1, LED4_5.1, LED5_5.1, LED6_5.1, LED7_5.1, LED8_5.1, LED9_5.1, LED10_5.1, LED11_5.1, LED12_5.1, LED13_5.1, LED14_5.1, LED15_5.1, LED16_5.1, P2_5.2, P3_5.12, R6_5.1, SW1_5.1, U1_5.B+
P6/3V3: J1_6.3, P3_6.6, P3_6.13, U1_6.3V3
P6/BAT+: P1_6.2, SW1_6.2
P6/BAT_SENSE: C1_6.1, R6_6.2, R7_6.1, TP1_6.2, U1_6.GP2
P6/BUZ_-: BZ1_6.2, Q1_6.3
P6/BUZ_G: Q1_6.1, R1_6.2, R2_6.1
P6/BUZ_IO: R1_6.1, TP1_6.5, U1_6.GP12
P6/DOCK_SENSE: C2_6.1, R8_6.2, R9_6.1, TP1_6.1, U1_6.GP1
P6/GND: C1_6.2, C2_6.2, C3_6.2, CL1_6.2, CL2_6.2, CL3_6.2, CL4_6.2, CL5_6.2, CL6_6.2, CL7_6.2, CL8_6.2, CL9_6.2, CL10_6.2, CL11_6.2, CL12_6.2, CL13_6.2, CL14_6.2, CL15_6.2, CL16_6.2, J1_6.1, J2_6.1, LED1_6.3, LED2_6.3, LED3_6.3, LED4_6.3, LED5_6.3, LED6_6.3, LED7_6.3, LED8_6.3, LED9_6.3, LED10_6.3, LED11_6.3, LED12_6.3, LED13_6.3, LED14_6.3, LED15_6.3, LED16_6.3, P1_6.1, P3_6.7, P3_6.14, Q1_6.2, Q2_6.2, R2_6.2, R4_6.2, R7_6.2, R9_6.2, U1_6.B-, U1_6.GND
P6/LED_D1: LED1_6.2, LED2_6.4
P6/LED_D2: LED2_6.2, LED3_6.4
P6/LED_D3: LED3_6.2, LED4_6.4
P6/LED_D4: LED4_6.2, LED5_6.4
P6/LED_D5: LED5_6.2, LED6_6.4
P6/LED_D6: LED6_6.2, LED7_6.4
P6/LED_D7: LED7_6.2, LED8_6.4
P6/LED_D8: LED8_6.2, LED9_6.4
P6/LED_D9: LED9_6.2, LED10_6.4
P6/LED_D10: LED10_6.2, LED11_6.4
P6/LED_D11: LED11_6.2, LED12_6.4
P6/LED_D12: LED12_6.2, LED13_6.4
P6/LED_D13: LED13_6.2, LED14_6.4
P6/LED_D14: LED14_6.2, LED15_6.4
P6/LED_D15: LED15_6.2, LED16_6.4
P6/LED_DIN: LED1_6.4, R5_6.2
P6/MOT_-: D1_6.2, P2_6.1, Q2_6.3
P6/MOT_G: Q2_6.1, R3_6.2, R4_6.1
P6/MOT_IO: R3_6.1, TP1_6.6, U1_6.GP13
P6/POGO5V: J2_6.2, R8_6.1, U1_6.5V
P6/RING_IO: R5_6.1, TP1_6.4, U1_6.GP5
P6/SPARE_GP3: P3_6.3, U1_6.GP3
P6/SPARE_GP6: P3_6.4, U1_6.GP6
P6/SPARE_GP7: P3_6.5, U1_6.GP7
P6/SPARE_GP8: P3_6.11, U1_6.GP8
P6/SPARE_GP9: P3_6.10, U1_6.GP9
P6/SPARE_GP10: P3_6.9, U1_6.GP10
P6/SPARE_GP11: P3_6.8, U1_6.GP11
P6/SPARE_RX: P3_6.2, U1_6.RX
P6/SPARE_TX: P3_6.1, U1_6.TX
P6/TOUCH: J1_6.2, TP1_6.3, U1_6.GP4
P6/VBAT: BZ1_6.1, C3_6.1, CL1_6.1, CL2_6.1, CL3_6.1, CL4_6.1, CL5_6.1, CL6_6.1, CL7_6.1, CL8_6.1, CL9_6.1, CL10_6.1, CL11_6.1, CL12_6.1, CL13_6.1, CL14_6.1, CL15_6.1, CL16_6.1, D1_6.1, LED1_6.1, LED2_6.1, LED3_6.1, LED4_6.1, LED5_6.1, LED6_6.1, LED7_6.1, LED8_6.1, LED9_6.1, LED10_6.1, LED11_6.1, LED12_6.1, LED13_6.1, LED14_6.1, LED15_6.1, LED16_6.1, P2_6.2, P3_6.12, R6_6.1, SW1_6.1, U1_6.B+

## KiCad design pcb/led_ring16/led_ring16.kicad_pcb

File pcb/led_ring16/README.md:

# 16-LED ring board (draft, for pricing)

**Status: laid out and routed, DRC clean (silkscreen notices only). Not ordered, not tested.**

| LED side | Back |
|---|---|
|  |  |

- 48 mm OD, 30 mm ID, 2 layers, 1.6 mm (same size as the 16-LED ring under consideration).
- 16 × XINGLIGHT XL-5050RGBC-2812B (LCSC C2843785, Extended), WS2812-compatible,
  3.5–5.5 V. KiCad's WS2812B footprint (pins 1 VDD, 2 DOUT, 3 GND, 4 DIN, same
  numbering as the XINGLIGHT datasheet); **check the LED orientation in JLCPCB's
  placement preview** — the datasheet's package drawing is an image only.
- 16 × 100 nF 0603 (C14663, Basic) on an inner circle, one per LED.
- Wire pads on a tab on the inside edge at 6 o'clock: **G D V** (GND, data in,
  VDD = VBAT), the same order as the carrier's RING connector. Data runs
  clockwise from LED 1 (just clockwise of the tab).
- No mounting holes: it sits in a tray in the base (to be designed).
- Bottom layer is a solid ground plane; LED numbers on the bottom silk.

Rebuild: `python3 build_ring.py && python3 ../carrier_s3/route_pcb.py led_ring16.kicad_pcb && sh export_fab.sh && sh render.sh ring_top.png ring_bottom.png`

Order files: `fab/led_ring16_gerbers.zip`, `fab/bom_jlc.csv`, `fab/cpl_jlc.csv`.

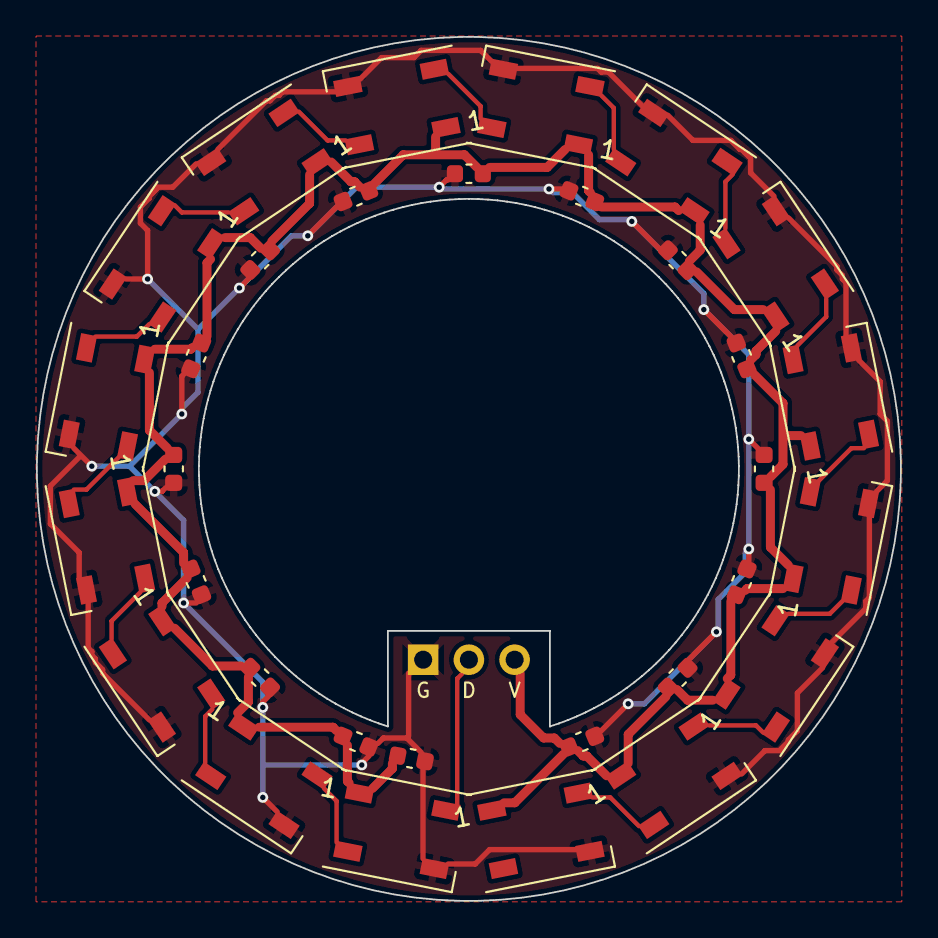
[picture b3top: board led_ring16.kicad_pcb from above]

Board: 2 copper layers, 48.0 x 48.0 mm, 33 parts (0 on the bottom side), 18 nets.

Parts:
C1, C2, C3, C4, C5, C6, C7, C8, C9, C10, C11, C12, C13, C14, C15, C16: 100nF; C_0603_1608Metric
D1, D2, D3, D4, D5, D6, D7, D8, D9, D10, D11, D12, D13, D14, D15, D16: XL-5050RGBC-2812B; LED_WS2812B_PLCC4_5.0x5.0mm_P3.2mm
J1: Ring wires

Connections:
D1: D1.2, D2.4
D2: D2.2, D3.4
D3: D3.2, D4.4
D4: D4.2, D5.4
D5: D5.2, D6.4
D6: D6.2, D7.4
D7: D7.2, D8.4
D8: D8.2, D9.4
D9: D9.2, D10.4
D10: D10.2, D11.4
D11: D11.2, D12.4
D12: D12.2, D13.4
D13: D13.2, D14.4
D14: D14.2, D15.4
D15: D15.2, D16.4
DIN: D1.4, J1.2
GND: C1.2, C2.2, C3.2, C4.2, C5.2, C6.2, C7.2, C8.2, C9.2, C10.2, C11.2, C12.2, C13.2, C14.2, C15.2, C16.2, D1.3, D2.3, D3.3, D4.3, D5.3, D6.3, D7.3, D8.3, D9.3, D10.3, D11.3, D12.3, D13.3, D14.3, D15.3, D16.3, J1.1
VDD: C1.1, C2.1, C3.1, C4.1, C5.1, C6.1, C7.1, C8.1, C9.1, C10.1, C11.1, C12.1, C13.1, C14.1, C15.1, C16.1, D1.1, D2.1, D3.1, D4.1, D5.1, D6.1, D7.1, D8.1, D9.1, D10.1, D11.1, D12.1, D13.1, D14.1, D15.1, D16.1, J1.3

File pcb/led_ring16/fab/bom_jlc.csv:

Comment,Designator,Footprint,LCSC Part #
XL-5050RGBC-2812B,"D1,D2,D3,D4,D5,D6,D7,D8,D9,D10,D11,D12,D13,D14,D15,D16",5050,C2843785
100nF,"C1,C2,C3,C4,C5,C6,C7,C8,C9,C10,C11,C12,C13,C14,C15,C16",0603,C14663

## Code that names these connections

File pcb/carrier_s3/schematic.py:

"""Draws schematic.svg / schematic.png from the circuit in design.py (by hand-placed sections, net labels join them)."""
import schemdraw
import schemdraw.elements as e

schemdraw.config(fontsize=11, lw=1.3)

def lab(d, txt, loc='right'):
    d += e.Label().label(txt, loc=loc, color='#1f4fbf')

def gnd(d):
    d += e.Ground()

with schemdraw.Drawing(file='schematic.svg', show=False) as d:
    d.config(unit=2)
    # ---------------- U1: SuperMini block ----------------
    U = e.Ic(pins=[e.IcPin(name='5V', side='left'), e.IcPin(name='GND', side='left'), e.IcPin(name='3V3', side='left'),
                   e.IcPin(name='B+', side='left'), e.IcPin(name='B-', side='left'),
                   e.IcPin(name='GP1', side='right'), e.IcPin(name='GP2', side='right'), e.IcPin(name='GP4', side='right'),
                   e.IcPin(name='GP5', side='right'), e.IcPin(name='GP12', side='right'), e.IcPin(name='GP13', side='right')],
             size=(3.4, 6.5), pinspacing=1.0, edgepadW=0.5).label('U1\nESP32-S3\nSuperMini', 'center')
    d += U.at((0, 0))
    for pin, net in [('5V', 'POGO5V'), ('GND', 'GND'), ('3V3', '3V3'), ('B+', 'VBAT (wire, H1)'), ('B-', 'GND (wire, H2)')]:
        d += e.Line().at(getattr(U, pin)).left(1.2)
        lab(d, net, 'left')
    for pin, net in [('GP1', 'DOCK_SENSE'), ('GP2', 'BAT_SENSE'), ('GP4', 'TOUCH'), ('GP5', 'RING_IO'), ('GP12', 'BUZ_IO'), ('GP13', 'MOT_IO')]:
        d += e.Line().at(getattr(U, pin)).right(1.2)
        lab(d, net, 'right')

    # ---------------- Power in ----------------
    d.here = (-14, 0)
    d += (J1 := e.Dot(open=True).label('J1 battery +', 'left'))
    d += e.Line().right(1)
    d += e.Switch().right().label('SW1 power')
    d += e.Line().right(0.5)
    lab(d, 'VBAT')
    d.here = (-14, -1.5)
    d += e.Dot(open=True).label('J1 battery −', 'left')
    d += e.Line().right(1)
    lab(d, 'GND')
    d.here = (-14, -3.5)
    d += e.Dot(open=True).label('J5 pogo 5V', 'left')
    d += e.Line().right(1.5)
    lab(d, 'POGO5V')
    d.here = (-14, -5)
    d += e.Dot(open=True).label('J5 pogo GND', 'left')
    d += e.Line().right(1.5)
    lab(d, 'GND')

    # ---------------- Dividers ----------------
    for i, (top, mid, rt, rb, c) in enumerate([('VBAT', 'BAT_SENSE', 'R6 100k', 'R7 100k', 'C1 100n'),
                                              ('POGO5V', 'DOCK_SENSE', 'R8 100k', 'R9 100k', 'C2 100n')]):
        x = -14 + i * 5; y = -8
        d.here = (x, y)
        d += e.Label().label(top, 'top', color='#1f4fbf')
        d += e.Resistor().down().label(rt, 'left')
        d += (m := e.Dot())
        d += e.Resistor().down().label(rb, 'left')
        gnd(d)
        d += e.Line().at(m.center).right(1.5)
        d += (n := e.Dot())
        d += e.Capacitor().down().label(c, 'right')
        gnd(d)
        d += e.Line().at(n.center).right(0.8)
        lab(d, mid)

    # ---------------- Buzzer / motor drivers (low-side N-MOSFET) ----------------
    for i, (io, rg, rp, q, load, motor) in enumerate([
            ('BUZ_IO', 'R1 100', 'R2 100k', 'Q1 AO3400A', 'BZ1 buzzer', False),
            ('MOT_IO', 'R3 100', 'R4 100k', 'Q2 AO3400A', 'J3 motor', True)]):
        x = 8 + i * 12; y = -10
        Q = e.NFet().right().at((x + 5, y)).label(q, 'right')
        d += Q
        # gate: IO -> resistor -> gate, pull-down from gate to GND
        d.here = (x, Q.gate[1])
        d += e.Label().label(io, 'left', color='#1f4fbf')
        d += e.Resistor().right().label(rg, 'top')
        d += (gd := e.Dot())
        d += e.Line().to(Q.gate)
        d += e.Resistor().at(gd.center).down().label(rp, 'left')
        gnd(d)
        # source to GND
        d += e.Line().at(Q.source).down(0.4)
        gnd(d)
        # drain -> load -> VBAT
        d += e.Line().at(Q.drain).up(0.6)
        d += (dd := e.Dot())
        if motor:
            d += e.Motor().up().label(load, 'right')
        else:
            d += e.RBox().up().label(load + ' (+ top)', 'right')
        d += (vt := e.Dot())
        d += e.Line().up(1.2)
        lab(d, 'VBAT', 'top')
        if motor:
            d += e.Line().at(dd.center).left(2)
            d += e.Diode().up().reverse().toy(vt.center).label('D1 B5819W', 'left')
            d += e.Line().to(vt.center)

    # ---------------- Ring, touch ----------------
    x, y = 8, -18
    d.here = (x, y)
    d += e.Label().label('RING_IO', 'left', color='#1f4fbf')
    d += e.Resistor().right().label('R5 330')
    d += e.Line().right(1)
    d += e.Dot(open=True).label('J2 ring DATA', 'right')
    d.here = (x, y - 1.5)
    d += e.Label().label('VBAT', 'left', color='#1f4fbf')
    d += e.Line().right(4)
    d += (vr := e.Dot())
    d += e.Line().right(1)
    d += e.Dot(open=True).label('J2 ring VCC', 'right')
    d += e.Capacitor().at(vr.center).down().label('C3, C4 2×47µ', 'right')
    gnd(d)
    d.here = (x, y - 5)
    d += e.Label().label('GND', 'left', color='#1f4fbf')
    d += e.Line().right(5)
    d += e.Dot(open=True).label('J2 ring GND', 'right')

    d.here = (x + 14, y)
    d += e.Label().label('3V3', 'left', color='#1f4fbf'); d += e.Line().right(1.5); d += e.Dot(open=True).label('J4 touch VCC', 'right')
    d.here = (x + 14, y - 1.5)
    d += e.Label().label('TOUCH', 'left', color='#1f4fbf'); d += e.Line().right(1.5); d += e.Dot(open=True).label('J4 touch OUT', 'right')
    d.here = (x + 14, y - 3)
    d += e.Label().label('GND', 'left', color='#1f4fbf'); d += e.Line().right(1.5); d += e.Dot(open=True).label('J4 touch GND', 'right')
    d.here = (x + 14, y - 5)
    d += e.Label().label('VBAT', 'left', color='#1f4fbf'); d += e.Line().right(1.5); d += e.Dot(open=True).label('J3 motor +', 'right')

    d += e.Label().at((-14, 6)).label('Pager carrier board, ESP32-S3 SuperMini (draft, not yet built). Blue labels with the same name are connected.', 'right')
